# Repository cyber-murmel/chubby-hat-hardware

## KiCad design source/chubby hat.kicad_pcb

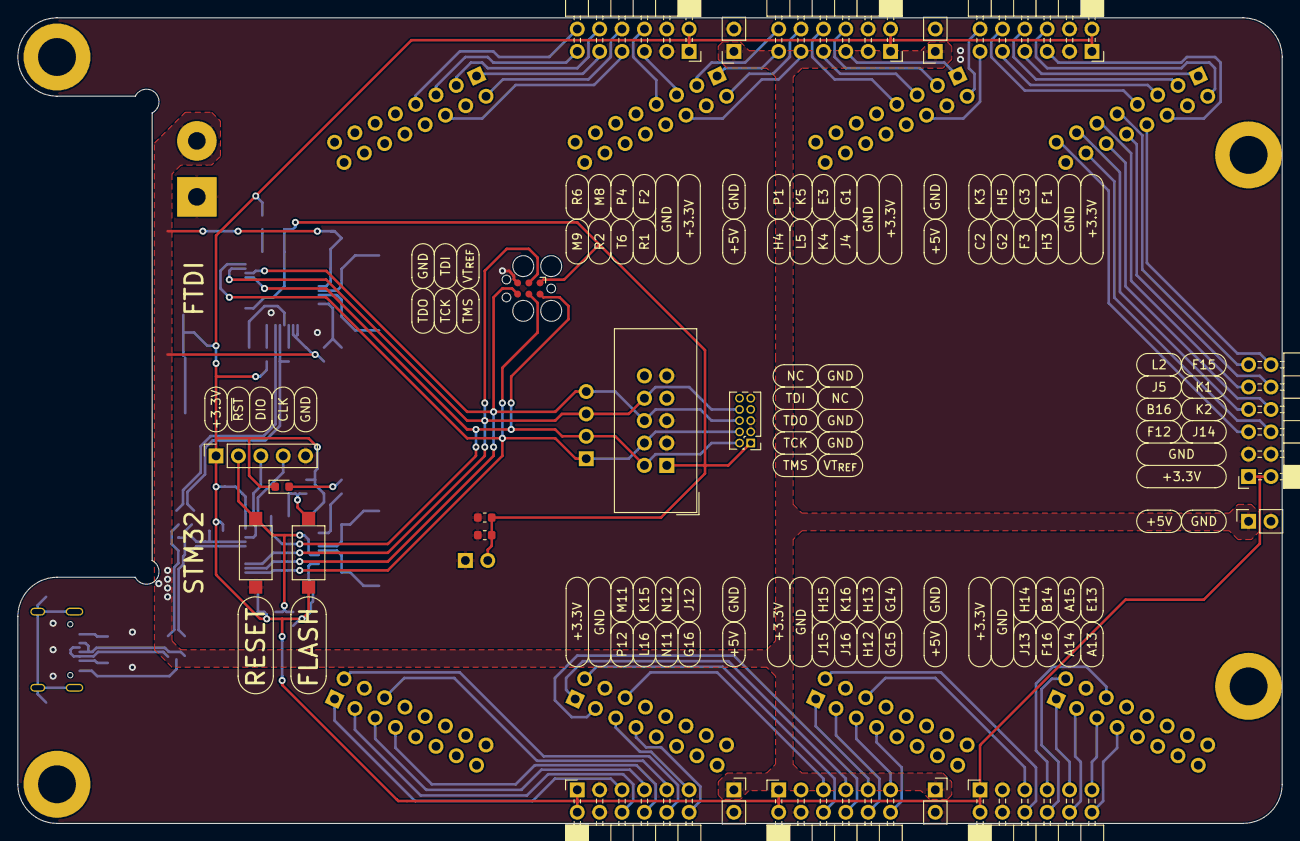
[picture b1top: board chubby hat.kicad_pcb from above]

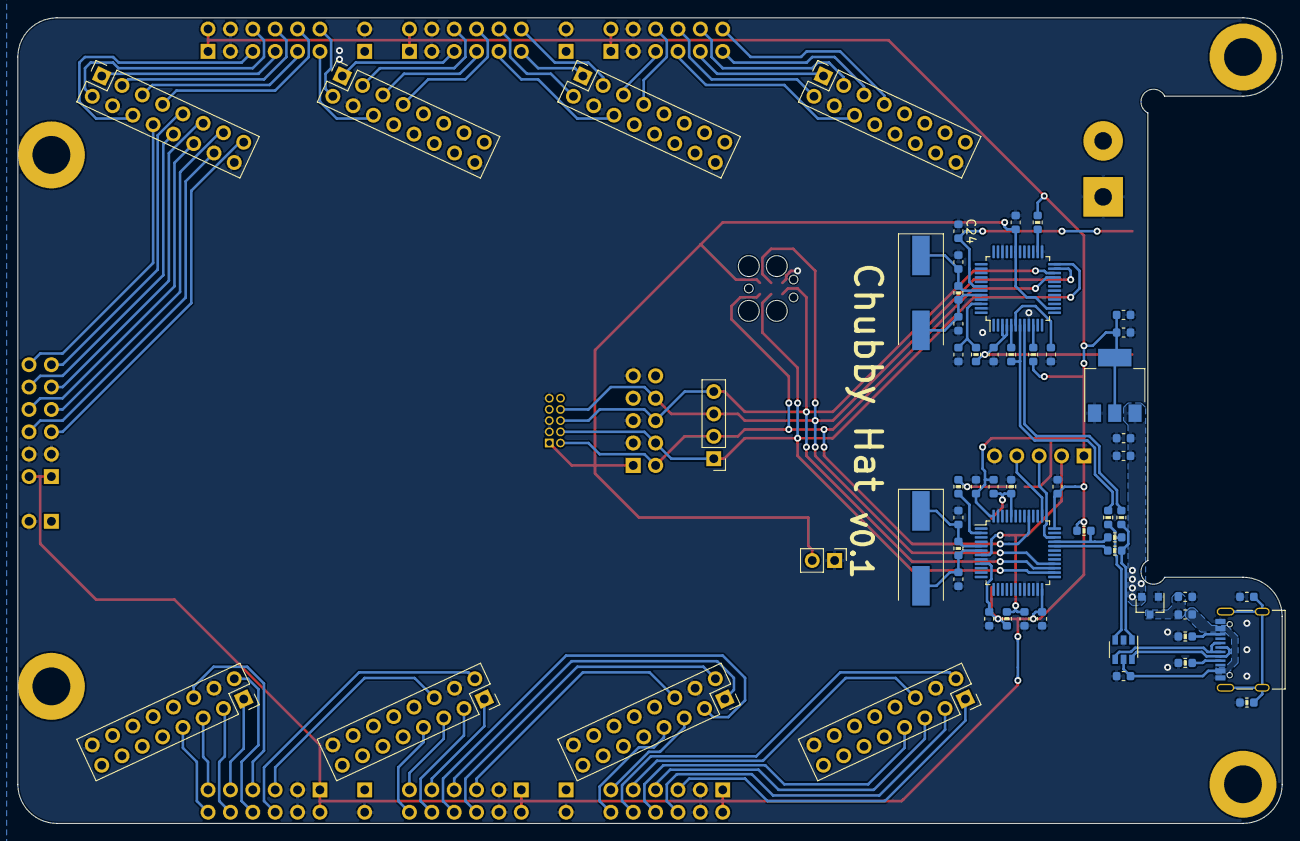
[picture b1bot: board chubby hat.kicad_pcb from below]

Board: 2 copper layers, 143.5 x 91.4 mm, 84 parts (58 on the bottom side), 92 nets.

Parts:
C1, C2, C3, C4, C6, C9, C10, C11, C12, C13, C14, C19, C20, C22, C23, C24: 100n; C_0603_1608Metric_Icon
C5, C7, C8, C21: 1u; C_0603_1608Metric_Icon
C15, C16, C17, C18: 36p; C_0603_1608Metric_Icon
D1: pink; LED_0603_1608Metric
FB1: 600Ω@100MHz; L_0603_1608Metric
H1, H2, H3, H4: M4; MountingHole_4.3mm_M4_ISO7380_Pad
J1, J2, J3, J4, J5, J6, J7, J8: HUB75; PinSocket_2x08_P2.54mm_Vertical
J9: Screw_Terminal_01x02; SolderWirePad_1x02_P7.62mm_Drill2mm
J10: Conn_01x02; PinHeader_1x02_P2.54mm_Vertical
J11: Conn_01x04; PinHeader_1x04_P2.54mm_Vertical
J12: USB_C_Receptacle_USB2.0; USB_C_Receptacle_Palconn_UTC16-G
J13: Conn_ARM_JTAG_SWD_10; IDC-Header_2x05_P2.54mm_Vertical
J14: SWD; PinSocket_1x05_P2.54mm_Vertical
J15, J16, J17, J18, J19: 5V; PinSocket_1x02_P2.54mm_Vertical
J20: Conn_ARM_JTAG_SWD_10; PinHeader_2x05_P1.27mm_Vertical
J21: TC2030; Tag-Connect_TC2030-IDC-FP_2x03_P1.27mm_Vertical
Pmod1, Pmod2, Pmod3, Pmod4, Pmod5, Pmod6, Pmod7: Pmod_02x06_Host; PinSocket_2x06_P2.54mm_Horizontal
Q1: AO3401A; SOT-23
R1, R2: 27; R_0603_1608Metric_Icon
R3, R8, R9: 1M; R_0603_1608Metric_Icon
R6, R7: 20; R_0603_1608Metric_Icon
R10, R11: 5.1k; R_0603_1608Metric_Icon
R12, R16, R19, R20: 1.5k; R_0603_1608Metric_Icon
R13, R15, R17: 10k; R_0603_1608Metric_Icon
R18: 470; R_0603_1608Metric_Icon
SW2: reset; SW_SPST_CK_RS282G05A3
SW3: boot0; SW_SPST_CK_RS282G05A3
U1: FT2232D; LQFP-48_7x7mm_P0.5mm
U2: USBLC6-2SC6; SOT-23-6
U3: STM32F103C8Tx; LQFP-48_7x7mm_P0.5mm
U4: AMS1117-3.3; SOT-223-3_TabPin2
Y1: 6MHz; Crystal_SMD_HC49-SD
Y2: 8MHz; Crystal_SMD_HC49-SD

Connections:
+3V3: C8.2, C9.2, C10.2, C11.2, C12.2, C13.2, C23.1, D1.1 (K), J14.1, Pmod1.1 (VCC), Pmod1.2 (VCC), Pmod2.1 (VCC), Pmod2.2 (VCC), Pmod3.1 (VCC), Pmod3.2 (VCC), Pmod4.1 (VCC), Pmod4.2 (VCC), Pmod5.1 (VCC), Pmod5.2 (VCC), Pmod6.1 (VCC), Pmod6.2 (VCC), Pmod7.1 (VCC), Pmod7.2 (VCC), R12.2, R13.2, R19.1, R20.1, SW3.1, U3.9 (VDDA), U3.24 (VDD), U3.36 (VDD), U3.48 (VDD), U4.2 (VO)
+5V: C6.2, C7.2, C20.2, C24.2, J9.2, J15.1, J16.1, J17.1, J18.1, J19.1, Q1.2 (S), R18.2, U1.3 (VCC), U1.4 (~RESET), U1.42 (VCC), U4.3 (VI)
/Blue Pill/BOOT0: C23.2, R15.1, SW3.2, U3.44 (BOOT0)
/Blue Pill/D_N: R7.2, U3.32 (PA11)
/Blue Pill/D_P: R6.1, R12.1, U3.33 (PA12)
/Blue Pill/OSCIN: C15.2, R3.1, U3.5 (PD0), Y2.1
/Blue Pill/OSCOUT: C16.2, R3.2, U3.6 (PD1), Y2.2
/Blue Pill/STM32_~RESET: C14.2, J14.2, R13.1, SW2.2, U3.7 (NRST)
/Blue Pill/SWCLK: J14.4, U3.37 (PA14)
/Blue Pill/SWDIO: J14.3, U3.34 (PA13)
/FTDI/D_N: R1.1, U1.8 (USBDM)
/FTDI/D_P: R2.2, R16.2, U1.7 (USBDP)
/JTAG.TCK: J11.1, J13.4 (SWDCLK/TCK), J20.4 (SWDCLK/TCK), J21.4, U1.24 (ADBUS0), U3.26 (PB13)
/JTAG.TDI: J11.3, J13.8 (NC/TDI), J20.8 (NC/TDI), J21.3, U1.23 (ADBUS1), U3.28 (PB15)
/JTAG.TDO: J11.4, J13.6 (SWO/TDO), J20.6 (SWO/TDO), J21.6, U1.22 (ADBUS2), U3.27 (PB14)
/JTAG.TMS: J11.2, J13.2 (SWDIO/TMS), J20.2 (SWDIO/TMS), J21.2, U1.21 (ADBUS3), U3.40 (PB4)
/Pmod1_IO1: J1.9, Pmod1.11 (IO1)
/Pmod1_IO2: J1.11, Pmod1.9 (IO2)
/Pmod1_IO3: J1.13, Pmod1.7 (IO3)
/Pmod1_IO4: J1.15, Pmod1.5 (IO4)
/Pmod1_IO5: J1.8, Pmod1.12 (IO5)
/Pmod1_IO6: J1.10, Pmod1.10 (IO6)
/Pmod1_IO7: J1.12, Pmod1.8 (IO7)
/Pmod1_IO8: J1.14, Pmod1.6 (IO8)
/Pmod2_IO1: J2.6, Pmod2.11 (IO1)
/Pmod2_IO2: J1.5, Pmod2.9 (IO2)
/Pmod2_IO3: J1.1, Pmod2.7 (IO3)
/Pmod2_IO4: J1.6, Pmod2.5 (IO4)
/Pmod2_IO5: J2.2, Pmod2.12 (IO5)
/Pmod2_IO6: J1.7, Pmod2.10 (IO6)
/Pmod2_IO7: J1.3, Pmod2.8 (IO7)
/Pmod2_IO8: J1.2, Pmod2.6 (IO8)
/Pmod3_IO1: J3.1, Pmod3.11 (IO1)
/Pmod3_IO2: J3.6, Pmod3.9 (IO2)
/Pmod3_IO3: J2.5, Pmod3.7 (IO3)
/Pmod3_IO4: J2.1, Pmod3.5 (IO4)
/Pmod3_IO5: J3.3, Pmod3.12 (IO5)
/Pmod3_IO6: J3.2, Pmod3.10 (IO6)
/Pmod3_IO7: J2.7, Pmod3.8 (IO7)
/Pmod3_IO8: J2.3, Pmod3.6 (IO8)
/Pmod4_IO1: J4.5, Pmod4.11 (IO1)
/Pmod4_IO2: J4.1, Pmod4.9 (IO2)
/Pmod4_IO3: J4.6, Pmod4.7 (IO3)
/Pmod4_IO4: J3.5, Pmod4.5 (IO4)
/Pmod4_IO5: J4.7, Pmod4.12 (IO5)
/Pmod4_IO6: J4.3, Pmod4.10 (IO6)
/Pmod4_IO7: J4.2, Pmod4.8 (IO7)
/Pmod4_IO8: J3.7, Pmod4.6 (IO8)
/Pmod5_IO1: J6.5, Pmod5.11 (IO1)
/Pmod5_IO2: J5.6, Pmod5.9 (IO2)
/Pmod5_IO3: J5.5, Pmod5.7 (IO3)
/Pmod5_IO4: J5.1, Pmod5.5 (IO4)
/Pmod5_IO5: J6.7, Pmod5.12 (IO5)
/Pmod5_IO6: J5.2, Pmod5.10 (IO6)
/Pmod5_IO7: J5.7, Pmod5.8 (IO7)
/Pmod5_IO8: J5.3, Pmod5.6 (IO8)
/Pmod6_IO1: J7.5, Pmod6.11 (IO1)
/Pmod6_IO2: J7.1, Pmod6.9 (IO2)
/Pmod6_IO3: J6.1, Pmod6.7 (IO3)
/Pmod6_IO4: J6.6, Pmod6.5 (IO4)
/Pmod6_IO5: J7.7, Pmod6.12 (IO5)
/Pmod6_IO6: J7.3, Pmod6.10 (IO6)
/Pmod6_IO7: J6.3, Pmod6.8 (IO7)
/Pmod6_IO8: J6.2, Pmod6.6 (IO8)
/Pmod7_IO1: J8.5, Pmod7.11 (IO1)
/Pmod7_IO2: J8.1, Pmod7.9 (IO2)
/Pmod7_IO3: J8.6, Pmod7.7 (IO3)
/Pmod7_IO4: J7.6, Pmod7.5 (IO4)
/Pmod7_IO5: J8.7, Pmod7.12 (IO5)
/Pmod7_IO6: J8.3, Pmod7.10 (IO6)
/Pmod7_IO7: J8.2, Pmod7.8 (IO7)
/Pmod7_IO8: J7.2, Pmod7.6 (IO8)
/Type C USB 2.0/D_N: J12.A7 (D-), J12.B7 (D-), U2.6 (IO1)
/Type C USB 2.0/D_P: J12.A6 (D+), J12.B6 (D+), U2.4 (IO2)
/USB.D+: R2.1, R6.2, U2.3 (IO2)
/USB.D-: R1.2, R7.1, U2.1 (IO1)
Earth: C3.1, J12.S1 (SHIELD), R9.2
GND: C1.2, C2.2, C3.2, C4.1, C5.1, C6.1, C7.1, C8.1, C9.1, C10.1, C11.1, C12.1, C13.1, C14.1, C15.1, C16.1, C17.1, C18.1, C19.1, C20.1, C21.1, C22.1, C24.1, J1.4, J1.16, J2.4, J2.16, J3.4, J3.16, J4.4, J4.16, J5.4, J5.16, J6.4, J6.16, J7.4, J7.16, J8.4, J8.16, J9.1, J10.1, J12.A1 (GND), J12.A12 (GND), J12.B1 (GND), J12.B12 (GND), J13.3 (GND), J13.5 (GND), J13.9 (GNDDetect), J14.5, J15.2, J16.2, J17.2, J18.2, J19.2, J20.3 (GND), J20.5 (GND), J20.9 (GNDDetect), J21.5, Pmod1.3 (GND), Pmod1.4 (GND), Pmod2.3 (GND), Pmod2.4 (GND), Pmod3.3 (GND), Pmod3.4 (GND), Pmod4.3 (GND), Pmod4.4 (GND), Pmod5.3 (GND), Pmod5.4 (GND), Pmod6.3 (GND), Pmod6.4 (GND), Pmod7.3 (GND), Pmod7.4 (GND), Q1.1 (G), R9.1, R10.1, R11.1, R15.2, SW2.1, U1.9 (GND), U1.18 (GND), U1.25 (GND), U1.34 (GND), U1.45 (AGND), U1.47 (TEST), U2.2 (GND), U3.8 (VSSA), U3.20 (PB2), U3.23 (VSS), U3.35 (VSS), U3.47 (VSS), U4.1 (GND)
unnamed: C2.1, U1.6 (3V3OUT)
unnamed: C5.2, FB1.1, Q1.3 (D)
unnamed: C17.2, R8.1, U1.43 (XTIN), Y1.1
unnamed: C18.2, R8.2, U1.44 (XTOUT), Y1.2
unnamed: C19.2, R18.1, U1.46 (AVCC)
unnamed: D1.2 (A), R17.2
unnamed: J12.A5 (CC1), R10.2
unnamed: J12.B5 (CC2), R11.2
unnamed: R16.1, U1.5 (~RSTOUT)
unnamed: R17.1, U3.2 (PC13)
unnamed: R19.2, U1.10 (SI/WUA)
unnamed: R20.2, U1.26 (SI/WUB)
VBUS: C4.2, FB1.2, J12.A4 (VBUS), J12.A9 (VBUS), J12.B4 (VBUS), J12.B9 (VBUS), U2.5 (VBUS)
VDD: C1.1, C21.2, C22.2, J10.2, J13.1 (VTref), J20.1 (VTref), J21.1, U1.14 (VCCIOA), U1.31 (VCCIOB)

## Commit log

2022-01-10 copied over old files
